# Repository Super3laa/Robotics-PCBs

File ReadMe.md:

# Robotics PCB

Some of PCB Designs during a robotics journey in college, There's more but i uploaded the cool ones, feel free to contact me about anything

### Tools
all of them deleoped using Eagle CAD.

### Open Source for Everyone Enjoy! :*

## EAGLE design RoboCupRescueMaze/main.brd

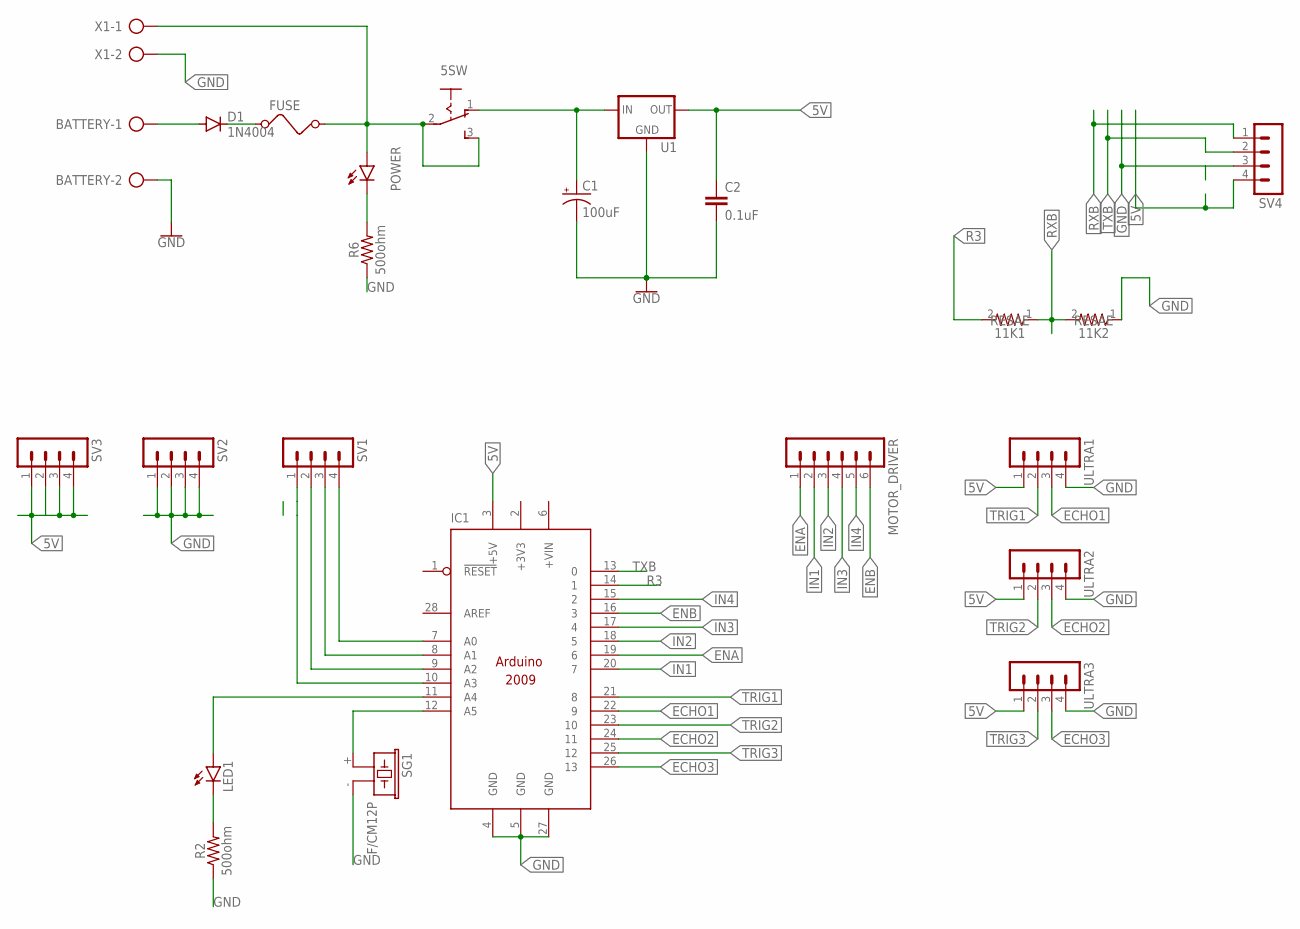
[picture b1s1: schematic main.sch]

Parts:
5SW: 255SB
11K1, 11K2: RESAE; RESAD846W63L520D250B
BATTERY: AK500/2-H
C1: 100uF; CPOL-RADIAL-2.5MM-6.5MM
C2: 0.1uF; CAP-PTH-SMALL-KIT
D1: 1N4004; DO41-10
FUSE: FUSE
IC1: ARDUINO2009_10; ARDUINO2009
LED1: LED10MM
MOTOR_DRIVER: MA06-1
POWER: LED3MM
R2, R6: 500ohm; AXIAL-0.3
SG1: F/CM12P
SV1, SV2, SV3, SV4: MA04-1
U1: 78XXS
ULTRA1, ULTRA2, ULTRA3: MA04-1
X1: AK500/2-H

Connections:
5V: C2.1, IC1.3 (+5V), SV3.1, SV3.2, SV3.3, SV3.4, SV4.4, U1.OUT, ULTRA1.1, ULTRA2.1, ULTRA3.1
+3V3: IC1.2 (+3V3)
BATTERYI: BATTERY.1, D1.A
ECHO1: IC1.22 (9), ULTRA1.3
ECHO2: IC1.24 (11), ULTRA2.3
ECHO3: IC1.26 (13), ULTRA3.3
ENA: IC1.19 (6), MOTOR_DRIVER.1
ENB: IC1.16 (3), MOTOR_DRIVER.6
GND: 11K2.1, BATTERY.2, C1.2 (-), C2.2, IC1.4 (GND), IC1.5 (GND), IC1.27 (GND), R2.P$1 (1), R6.P$1 (1), SG1.- (2), SV2.1, SV2.2, SV2.3, SV2.4, SV4.3, U1.GND, ULTRA1.4, ULTRA2.4, ULTRA3.4, X1.2
IN1: IC1.20 (7), MOTOR_DRIVER.2
IN2: IC1.18 (5), MOTOR_DRIVER.3
IN3: IC1.17 (4), MOTOR_DRIVER.4
IN4: IC1.15 (2), MOTOR_DRIVER.5
unnamed: IC1.7 (A0), SV1.4
unnamed: IC1.8 (A1), SV1.3
unnamed: IC1.9 (A2), SV1.2
unnamed: IC1.10 (A3), SV1.1
unnamed: IC1.11 (A4), LED1.A
unnamed: D1.C, FUSE.1
unnamed: POWER.K (C), R6.P$2 (2)
unnamed: 5SW.2, 5SW.3 (S), FUSE.2, POWER.A, X1.1
unnamed: LED1.K (C), R2.P$2 (2)
unnamed: IC1.12 (A5), SG1.+ (1)
R3: 11K1.2, IC1.14 (1)
RXB: 11K1.1, 11K2.2, SV4.1
SSS: 5SW.1 (O), C1.1 (+), U1.IN
TRIG1: IC1.21 (8), ULTRA1.2
TRIG2: IC1.23 (10), ULTRA2.2
TRIG3: IC1.25 (12), ULTRA3.2
TXB: IC1.13 (0), SV4.2

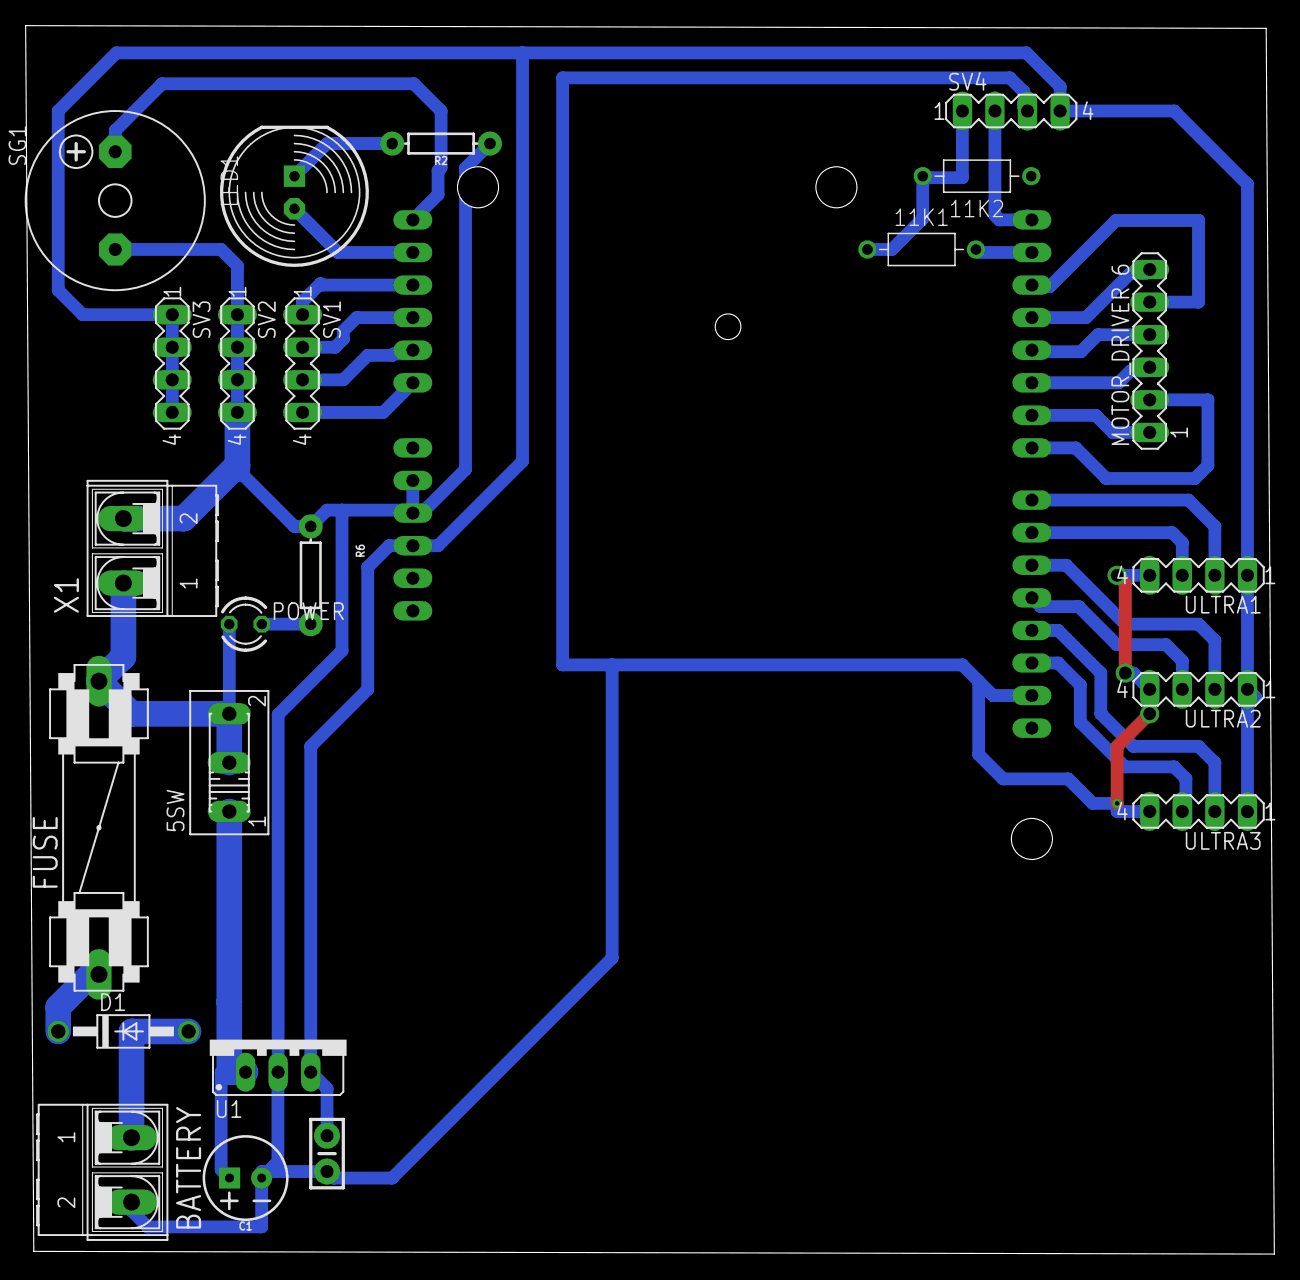
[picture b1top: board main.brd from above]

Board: 2 copper layers, 97.3 x 95.8 mm, 24 parts (1 on the bottom side), 29 nets.

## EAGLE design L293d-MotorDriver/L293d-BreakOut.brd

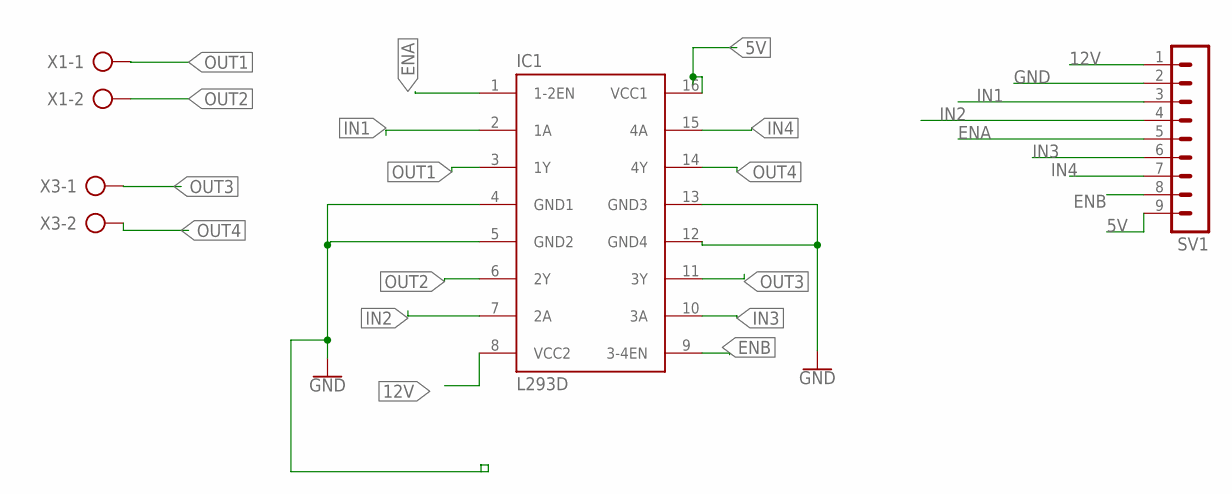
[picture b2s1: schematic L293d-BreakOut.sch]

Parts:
IC1: L293D; DIL16
SV1: MA09-1W
X1, X3: AK500/2-H

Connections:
5V: IC1.16 (VCC1), SV1.9
12V: IC1.8 (VCC2), SV1.1
ENA: IC1.1 (1-2EN), SV1.5
ENB: IC1.9 (3-4EN), SV1.8
GND: IC1.4 (GND1), IC1.5 (GND2), IC1.12 (GND4), IC1.13 (GND3), SV1.2
IN1: IC1.2 (1A), SV1.3
IN2: IC1.7 (2A), SV1.4
IN3: IC1.10 (3A), SV1.6
IN4: IC1.15 (4A), SV1.7
OUT1: IC1.3 (1Y), X1.1
OUT2: IC1.6 (2Y), X1.2
OUT3: IC1.11 (3Y), X3.1
OUT4: IC1.14 (4Y), X3.2

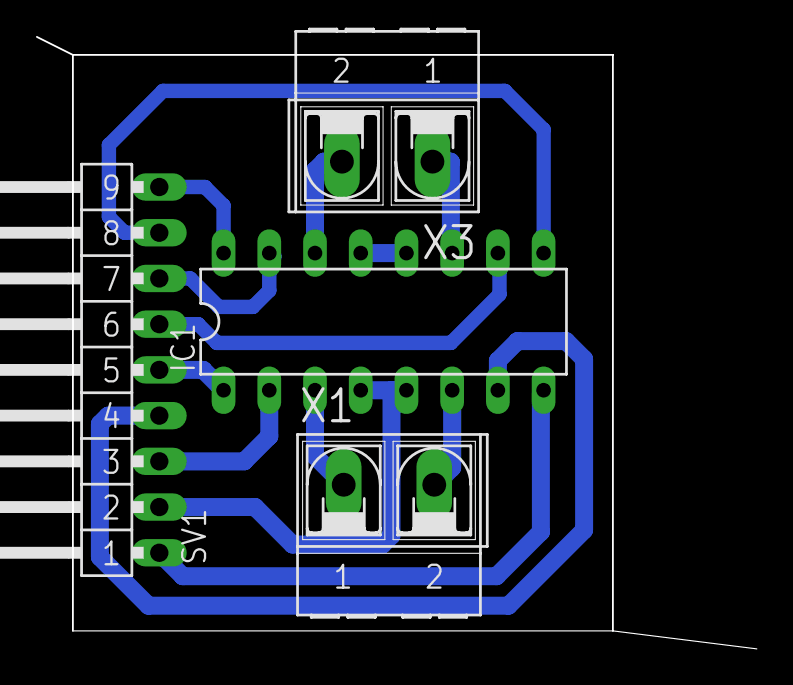
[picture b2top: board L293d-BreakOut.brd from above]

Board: 2 copper layers, 40.0 x 34.0 mm, 4 parts (0 on the bottom side), 13 nets.

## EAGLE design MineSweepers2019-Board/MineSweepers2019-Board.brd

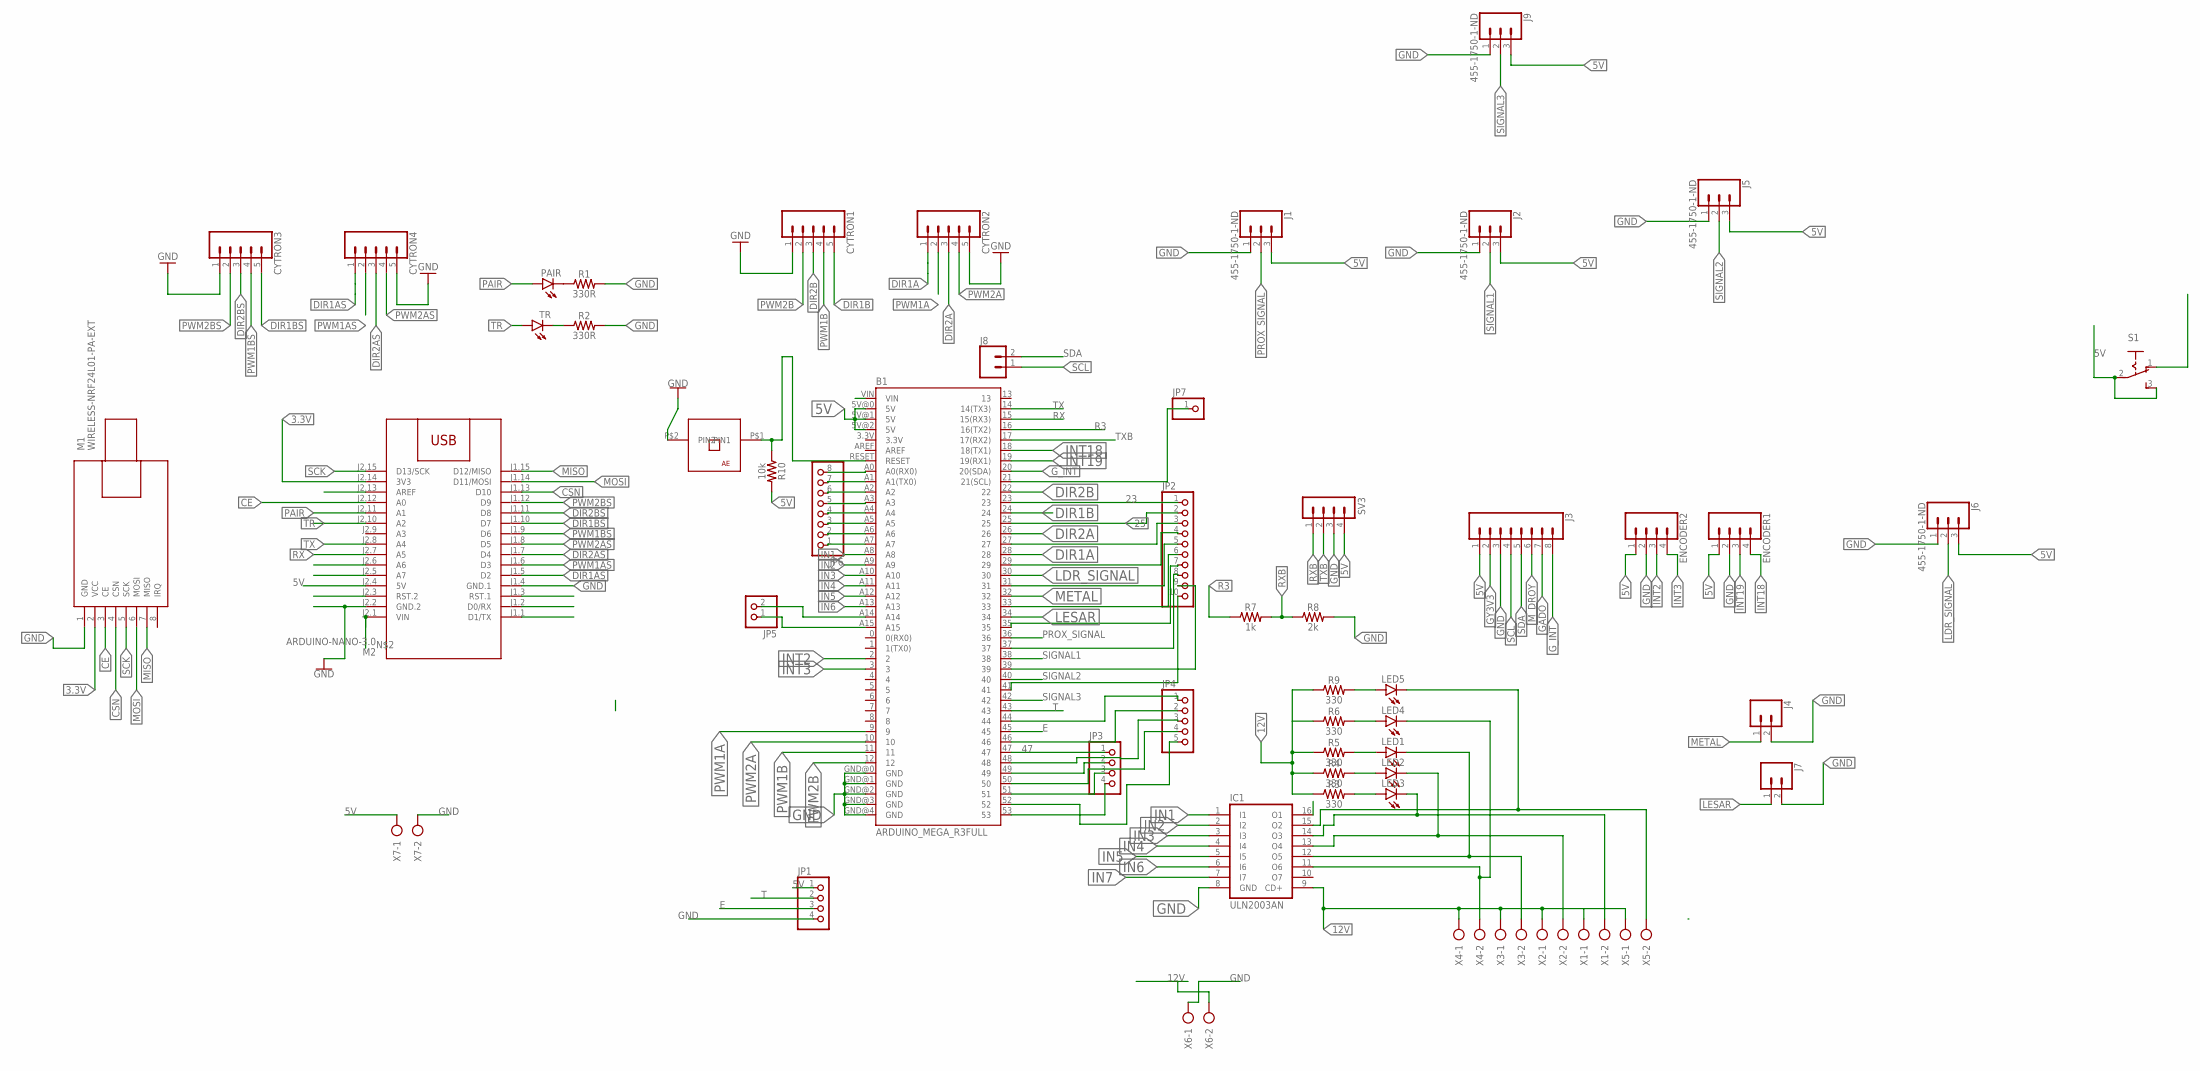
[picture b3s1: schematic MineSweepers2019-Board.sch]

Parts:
B1: ARDUINO_MEGA_R3FULL; ARDUINO_MEGA
CYTRON1, CYTRON2, CYTRON3, CYTRON4: CONN_05; 1X05
ENCODER1, ENCODER2: CONN_04; 1X04
IC1: ULN2003AN; DIL16
J1, J2, J5, J6, J9: 455-1750-1-ND; 1X03
J3: CONN_08"; 1X08
J4, J7, J8: CONN_02; 1X02
JP1, JP3: PINHD-1X4; 1X04
JP2: PINHD-1X10; 1X10
JP4: PINHD-1X5; 1X05
JP5: PINHD-1X2; 1X02
JP6: PINHD-1X8; 1X08
JP7: PINHD-1X1; 1X01
LED1, LED2, LED3, LED4, LED5: LED3MM
M1: WIRELESS-NRF24L01-PA-EXT
M2: ARDUINO-NANO-3.0
PAIR: LED3MM
R1, R2: 330R; AXIAL-0.3
R3, R4, R5, R6, R9: 330; AXIAL-0.3
R7: 1k; AXIAL-0.3
R8: 2k; AXIAL-0.3
R10: 10k; AXIAL-0.3
S1: 255SB
SV3: MA04-1
TR: LED3MM
U$1: PUSHBUTTON-AE
X1, X2, X3, X4, X5, X6, X7: AK500/2-H

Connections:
3.3V: M1.2 (VCC), M2.J2.14 (3V3)
5V: B1.5V@0 (5V), B1.5V@1 (5V), B1.5V@2 (5V), ENCODER1.1, ENCODER2.1, J1.3, J2.3, J3.1, J5.3, J6.3, J9.3, JP1.1, M2.J2.4 (5V), R10.P$2 (2), S1.2, S1.3 (S), SV3.4, X7.1
12V: IC1.9 (CD+), R3.P$1 (1), R4.P$1 (1), R5.P$1 (1), R6.P$1 (1), R9.P$1 (1), X1.1, X2.1, X3.1, X4.1, X5.1, X6.2
23: B1.23, JP2.1
25: B1.25, JP2.2
47: B1.47, JP3.1
CE: M1.3 (CE), M2.J2.12 (A0)
CSN: M1.4 (CSN), M2.J1.13 (D10)
DIR1A: B1.28, CYTRON2.1
DIR1AS: CYTRON4.1, M2.J1.5 (D2)
DIR1B: B1.24, CYTRON1.5
DIR1BS: CYTRON3.5, M2.J1.10 (D7)
DIR2A: B1.26, CYTRON2.3
DIR2AS: CYTRON4.3, M2.J1.7 (D4)
DIR2B: B1.22, CYTRON1.3
DIR2BS: CYTRON3.3, M2.J1.11 (D8)
E: B1.45, JP1.3
GADO: J3.7
GND: B1.GND@0 (GND), B1.GND@1 (GND), B1.GND@2 (GND), B1.GND@3 (GND), B1.GND@4 (GND), CYTRON1.1, CYTRON2.5, CYTRON3.1, CYTRON4.5, ENCODER1.2, ENCODER2.2, IC1.8 (GND), J1.1, J2.1, J3.3, J4.2, J5.1, J6.1, J7.2, J9.1, JP1.4, M1.1 (GND), M2.J1.4 (GND.1), M2.J2.2 (GND.2), R1.P$2 (2), R2.P$2 (2), R8.P$2 (2), SV3.3, U$1.P$2 (PIN2), X6.1, X7.2
GY3V3: J3.2
G_INT: B1.20 (20(SDA)), J3.8
IN1: B1.A8, IC1.1 (I1)
IN2: B1.A9, IC1.2 (I2)
IN3: B1.A10, IC1.3 (I3)
IN4: B1.A11, IC1.4 (I4)
IN5: B1.A12, IC1.5 (I5)
IN6: B1.A13, IC1.6 (I6)
IN7: IC1.7 (I7)
INT2: B1.2, ENCODER2.3
INT3: B1.3, ENCODER2.4
INT18: B1.18 (18(TX1)), ENCODER1.4
INT19: B1.19 (19(RX1)), ENCODER1.3
LDR_SIGNAL: B1.30, J6.2
LESAR: B1.34, J7.1
METAL: B1.32, J4.1
MISO: M1.7 (MISO), M2.J1.15 (D12/MISO)
MOSI: M1.6 (MOSI), M2.J1.14 (D11/MOSI)
M_DROY: J3.6
unnamed: LED5.A, R9.P$2 (2)
unnamed: PAIR.K (C), R1.P$1 (1)
unnamed: R2.P$1 (1), TR.K (C)
unnamed: B1.27, JP2.3
unnamed: IC1.13 (O4), LED2.K (C), X2.2
unnamed: IC1.14 (O3), LED3.K (C), X1.2
unnamed: IC1.12 (O5), LED1.K (C), X3.2
unnamed: B1.29, JP2.4
unnamed: B1.31, JP2.5
unnamed: B1.33, JP2.6
unnamed: B1.35, JP2.7
unnamed: LED3.A, R3.P$2 (2)
unnamed: LED2.A, R4.P$2 (2)
unnamed: B1.37, JP2.8
unnamed: LED1.A, R5.P$2 (2)
unnamed: B1.39, JP2.9
unnamed: B1.41, JP2.10
unnamed: B1.49, JP3.2
unnamed: B1.51, JP3.3
unnamed: LED4.A, R6.P$2 (2)
unnamed: B1.53, JP3.4
unnamed: B1.44, JP4.1
unnamed: B1.46, JP4.2
unnamed: B1.48, JP4.3
unnamed: B1.50, JP4.4
unnamed: B1.52, JP4.5
unnamed: B1.A1 (A1(TX0)), JP6.7
unnamed: B1.A2, JP6.6
unnamed: B1.A3, JP6.5
unnamed: B1.A4, JP6.4
unnamed: B1.A5, JP6.3
unnamed: B1.A6, JP6.2
unnamed: B1.A7, JP6.1
unnamed: B1.A0 (A0(RX0)), JP6.8
unnamed: B1.A14, JP5.2
unnamed: B1.A15, JP5.1
unnamed: B1.21 (21(SCL)), JP7.1
unnamed: B1.RESET, R10.P$1 (1), U$1.P$1 (PIN1)
O1: IC1.15 (O2), LED5.K (C), X5.2
O2: IC1.16 (O1)
O6: IC1.11 (O6), LED4.K (C), X4.2
PAIR: M2.J2.11 (A1), PAIR.A
PROX_SIGNAL: B1.36, J1.2
PWM1A: B1.9, CYTRON2.2
PWM1AS: CYTRON4.2, M2.J1.6 (D3)
PWM1B: B1.11, CYTRON1.4
PWM1BS: CYTRON3.4, M2.J1.9 (D6)
PWM2A: B1.10, CYTRON2.4
PWM2AS: CYTRON4.4, M2.J1.8 (D5)
PWM2B: B1.12, CYTRON1.2
PWM2BS: CYTRON3.2, M2.J1.12 (D9)
R3: B1.16 (16(TX2)), R7.P$1 (1)
RX: B1.15 (15(RX3)), M2.J2.7 (A5)
RXB: R7.P$2 (2), R8.P$1 (1), SV3.1
SCK: M1.5 (SCK), M2.J2.15 (D13/SCK)
SCL: J3.4, J8.1
SDA: J3.5, J8.2
SIGNAL1: B1.38, J2.2
SIGNAL2: B1.40, J5.2
SIGNAL3: B1.42, J9.2
T: B1.43, JP1.2
TR: M2.J2.10 (A2), TR.A
TX: B1.14 (14(TX3)), M2.J2.8 (A4)
TXB: B1.17 (17(RX2)), SV3.2
VIN: B1.VIN

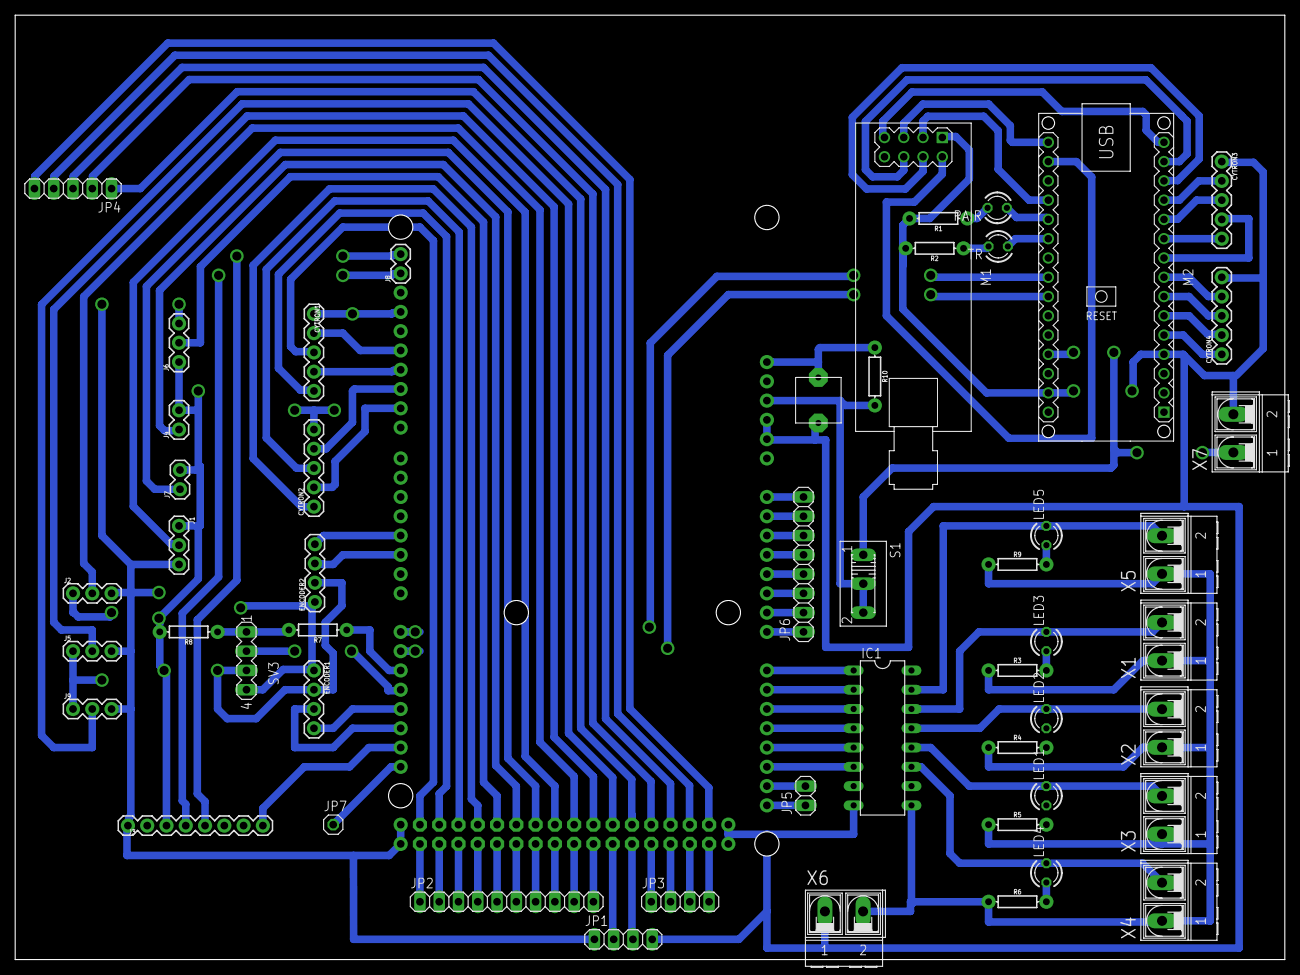
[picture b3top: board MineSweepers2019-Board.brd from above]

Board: 2 copper layers, 167.3 x 124.5 mm, 53 parts (1 on the bottom side), 97 nets.

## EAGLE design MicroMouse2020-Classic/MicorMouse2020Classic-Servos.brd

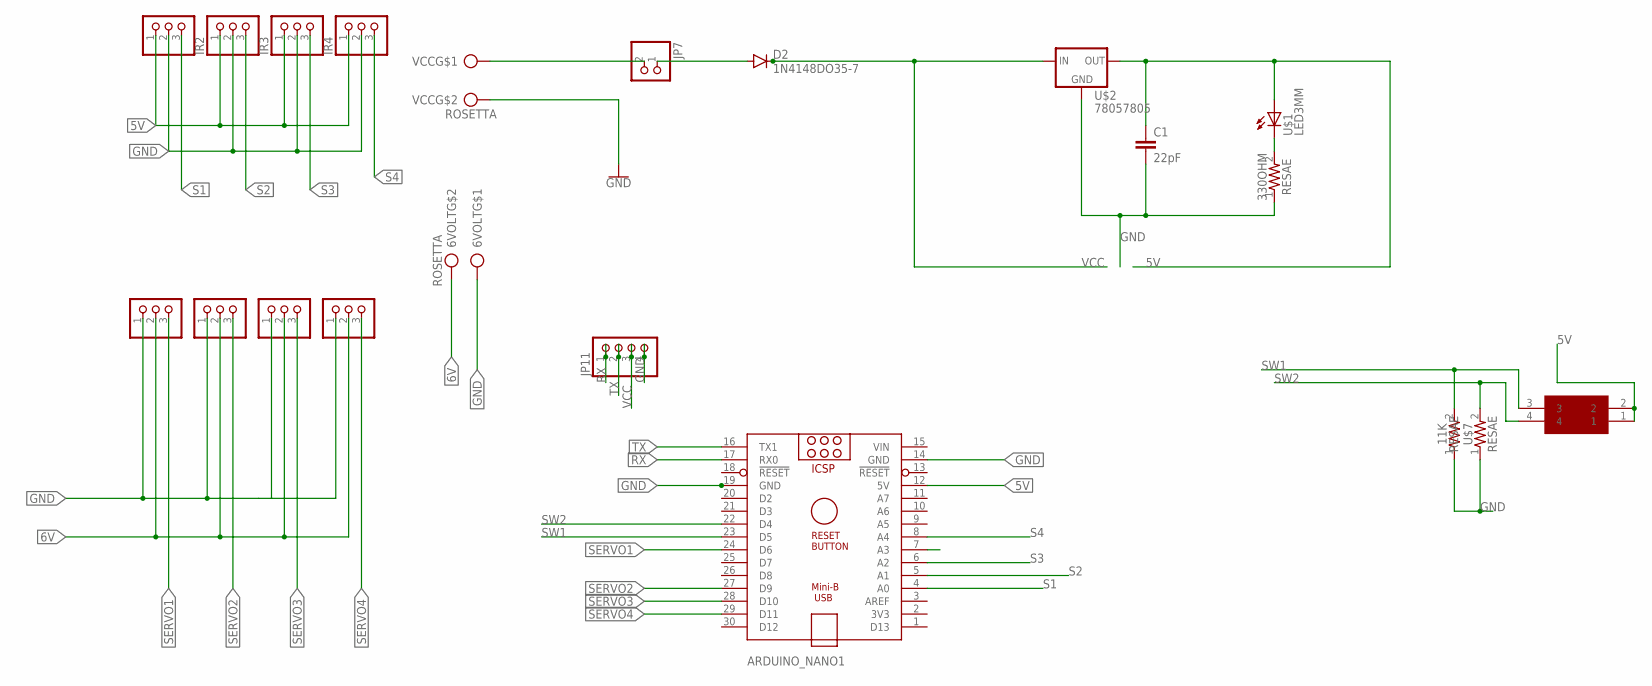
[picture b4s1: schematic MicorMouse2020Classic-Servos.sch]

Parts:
6VOLT: ROSETTA; AK550/2
11K, 330OHM: RESAE; RESAD846W63L520D250B
ARDUINO_NANO1: ARDUINO_NANO
C1: 22pF; CAP-PTH-2.54
D2: 1N4148DO35-7; DO35-7
IR1, IR2, IR3, IR4: PINHD-1X3; 1X03
JP7: PINHD-1X2; 1X02
JP11: PINHD-1X4/90; 1X04/90
SERVO1, SERVO2, SERVO3, SERVO4: PINHD-1X3; 1X03
U$1: LED3MM; LEDRD254W60D310H860B
U$2: 78057805; T-30_V
U$7: RESAE; RESAD846W63L520D250B
U$8: AE-DIP; EPG-02
VCC: ROSETTA; AK550/2

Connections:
5V: ARDUINO_NANO1.12 (5V), C1.1, IR1.1, IR2.1, IR3.1, IR4.1, U$1.A, U$2.3 (OUT), U$8.1, U$8.2
6V: 6VOLT.2, SERVO1.2, SERVO2.2, SERVO3.2, SERVO4.2
GND: 6VOLT.1, 11K.1, 330OHM.1, ARDUINO_NANO1.14 (GND), ARDUINO_NANO1.19 (GND), C1.2, IR1.2, IR2.2, IR3.2, IR4.2, JP11.4, SERVO1.1, SERVO2.1, SERVO3.1, SERVO4.1, U$2.2 (GND), U$7.1, VCC.2
unnamed: JP7.2, VCC.1
unnamed: D2.A, JP7.1
unnamed: 330OHM.2, U$1.C
RX: ARDUINO_NANO1.17 (RX0), JP11.1
S1: ARDUINO_NANO1.4 (A0), IR1.3
S2: ARDUINO_NANO1.5 (A1), IR2.3
S3: ARDUINO_NANO1.6 (A2), IR3.3
S4: ARDUINO_NANO1.8 (A4), IR4.3
SERVO1: ARDUINO_NANO1.24 (D6), SERVO4.3
SERVO2: ARDUINO_NANO1.27 (D9), SERVO3.3
SERVO3: ARDUINO_NANO1.28 (D10), SERVO2.3
SERVO4: ARDUINO_NANO1.29 (D11), SERVO1.3
SW1: 11K.2, ARDUINO_NANO1.23 (D5), U$8.3
SW2: ARDUINO_NANO1.22 (D4), U$7.2, U$8.4
TX: ARDUINO_NANO1.16 (TX1), JP11.2
VCC: D2.C, JP11.3, U$2.1 (IN)
VIN: ARDUINO_NANO1.15 (VIN)

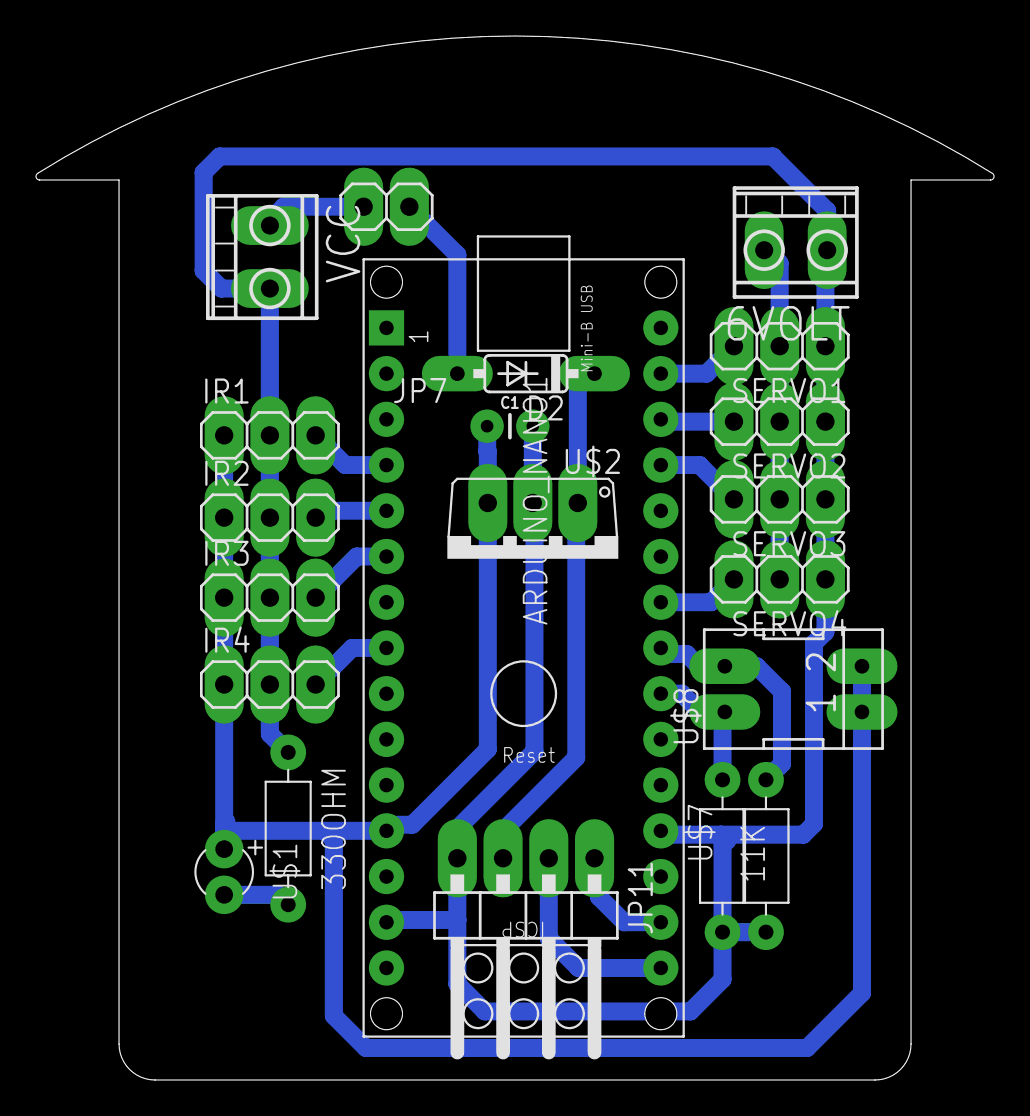
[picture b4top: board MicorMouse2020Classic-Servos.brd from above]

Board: 2 copper layers, 53.2 x 58.0 mm, 21 parts (0 on the bottom side), 19 nets.

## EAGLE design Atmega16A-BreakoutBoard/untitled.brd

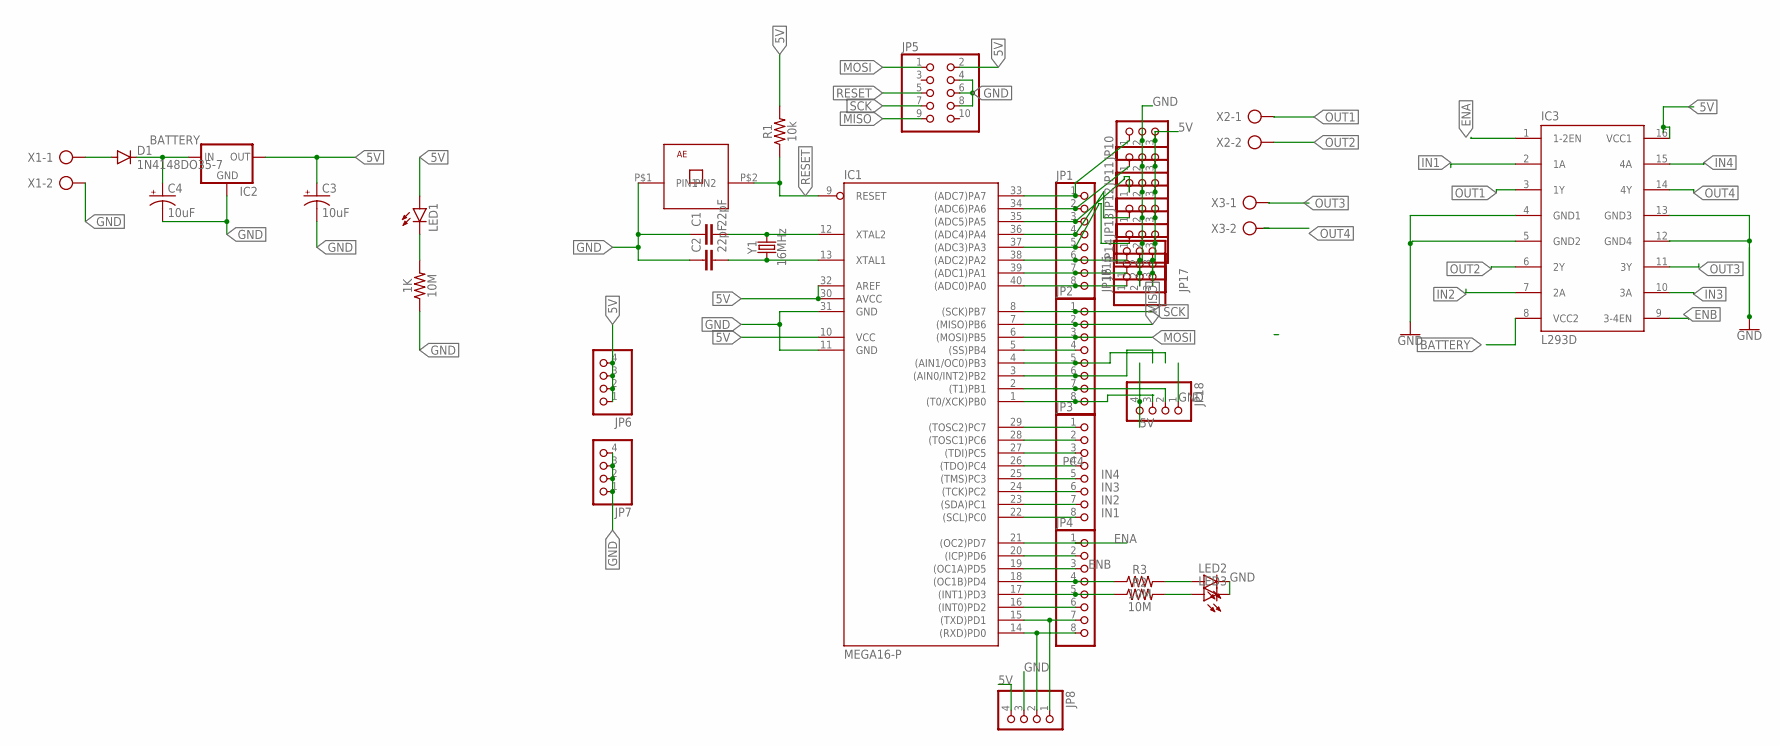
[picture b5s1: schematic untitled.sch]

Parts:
1K: 10M; AXIAL-0.3
C1, C2: 22pF; CAP-PTH-2.54
C3, C4: 10uF; CPOL-RADIAL-2.5MM-5MM
D1: 1N4148DO35-7; DO35-7
IC1: MEGA16-P; DIL40
IC2: 78XXS
IC3: L293D; DIL16
JP1, JP2, JP3, JP4: PINHD-1X8; 1X08
JP5: PINHD-2X5; 2X05
JP6, JP7, JP8, JP18: PINHD-1X4; 1X04
JP10, JP11, JP12, JP13, JP14, JP15, JP16, JP17: PINHD-1X3; 1X03
LED1, LED2, LED3: LED3MM
R1: 10k; AXIAL-0.3
R2, R3: 10M; AXIAL-0.3
U$1: PUSHBUTTON-AE
X1, X2, X3: AK500/2-H
Y1: 16MHz; HC49US

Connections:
5V: C3.1 (+), IC1.10 (VCC), IC1.30 (AVCC), IC1.32 (AREF), IC2.OUT, IC3.16 (VCC1), JP5.2, JP6.1, JP6.2, JP6.3, JP6.4, JP8.4, JP10.3, JP11.3, JP12.3, JP13.3, JP14.3, JP15.3, JP16.3, JP17.3, JP18.4, LED1.A, R1.P$2 (2)
BATTERY: C4.1 (+), D1.C, IC2.IN, IC3.8 (VCC2)
ENA: IC1.21 ((OC2)PD7), IC3.1 (1-2EN), JP4.1
ENB: IC1.19 ((OC1A)PD5), IC3.9 (3-4EN), JP4.3
GND: 1K.P$1 (1), C1.1, C2.1, C3.2 (-), C4.2 (-), IC1.11 (GND), IC1.31 (GND), IC2.GND, IC3.4 (GND1), IC3.5 (GND2), IC3.12 (GND4), IC3.13 (GND3), JP5.4, JP5.6, JP5.8, JP7.1, JP7.2, JP7.3, JP7.4, JP8.3, JP10.2, JP11.2, JP12.2, JP13.2, JP14.2, JP15.2, JP16.2, JP17.2, JP18.1, LED2.K (C), LED3.K (C), U$1.P$1 (PIN1), X1.2
IN1: IC1.22 ((SCL)PC0), IC3.2 (1A), JP3.8
IN2: IC1.23 ((SDA)PC1), IC3.7 (2A), JP3.7
IN3: IC1.24 ((TCK)PC2), IC3.10 (3A), JP3.6
IN4: IC1.25 ((TMS)PC3), IC3.15 (4A), JP3.5
MISO: IC1.7 ((MISO)PB6), JP2.2, JP5.9
MOSI: IC1.6 ((MOSI)PB5), JP2.3, JP5.1
unnamed: C1.2, IC1.12 (XTAL2), Y1.2
unnamed: C2.2, IC1.13 (XTAL1), Y1.1
unnamed: LED2.A, R3.P$2 (2)
unnamed: 1K.P$2 (2), LED1.K (C)
unnamed: LED3.A, R2.P$2 (2)
unnamed: D1.A, X1.1
unnamed: IC1.33 ((ADC7)PA7), JP1.1, JP10.1
unnamed: IC1.34 ((ADC6)PA6), JP1.2, JP11.1
unnamed: IC1.35 ((ADC5)PA5), JP1.3, JP12.1
unnamed: IC1.36 ((ADC4)PA4), JP1.4, JP13.1
unnamed: IC1.37 ((ADC3)PA3), JP1.5, JP14.1
unnamed: IC1.38 ((ADC2)PA2), JP1.6, JP15.1
unnamed: IC1.39 ((ADC1)PA1), JP1.7, JP16.1
unnamed: IC1.40 ((ADC0)PA0), JP1.8, JP17.1
unnamed: IC1.5 ((SS)PB4), JP2.4
unnamed: IC1.4 ((AIN1/OC0)PB3), JP2.5
unnamed: IC1.3 ((AIN0/INT2)PB2), JP2.6
unnamed: IC1.2 ((T1)PB1), JP2.7, JP18.2
unnamed: IC1.1 ((T0/XCK)PB0), JP2.8, JP18.3
unnamed: IC1.29 ((TOSC2)PC7), JP3.1
unnamed: IC1.28 ((TOSC1)PC6), JP3.2
unnamed: IC1.27 ((TDI)PC5), JP3.3
unnamed: IC1.20 ((ICP)PD6), JP4.2
unnamed: IC1.18 ((OC1B)PD4), JP4.4, R3.P$1 (1)
unnamed: IC1.17 ((INT1)PD3), JP4.5, R2.P$1 (1)
unnamed: IC1.16 ((INT0)PD2), JP4.6
OUT1: IC3.3 (1Y), X2.1
OUT2: IC3.6 (2Y), X2.2
OUT3: IC3.11 (3Y), X3.1
OUT4: IC3.14 (4Y), X3.2
PC4: IC1.26 ((TDO)PC4), JP3.4
RESET: IC1.9 (RESET), JP5.5, R1.P$1 (1), U$1.P$2 (PIN2)
RX: IC1.14 ((RXD)PD0), JP4.8, JP8.2
SCK: IC1.8 ((SCK)PB7), JP2.1, JP5.7
TX: IC1.15 ((TXD)PD1), JP4.7, JP8.1

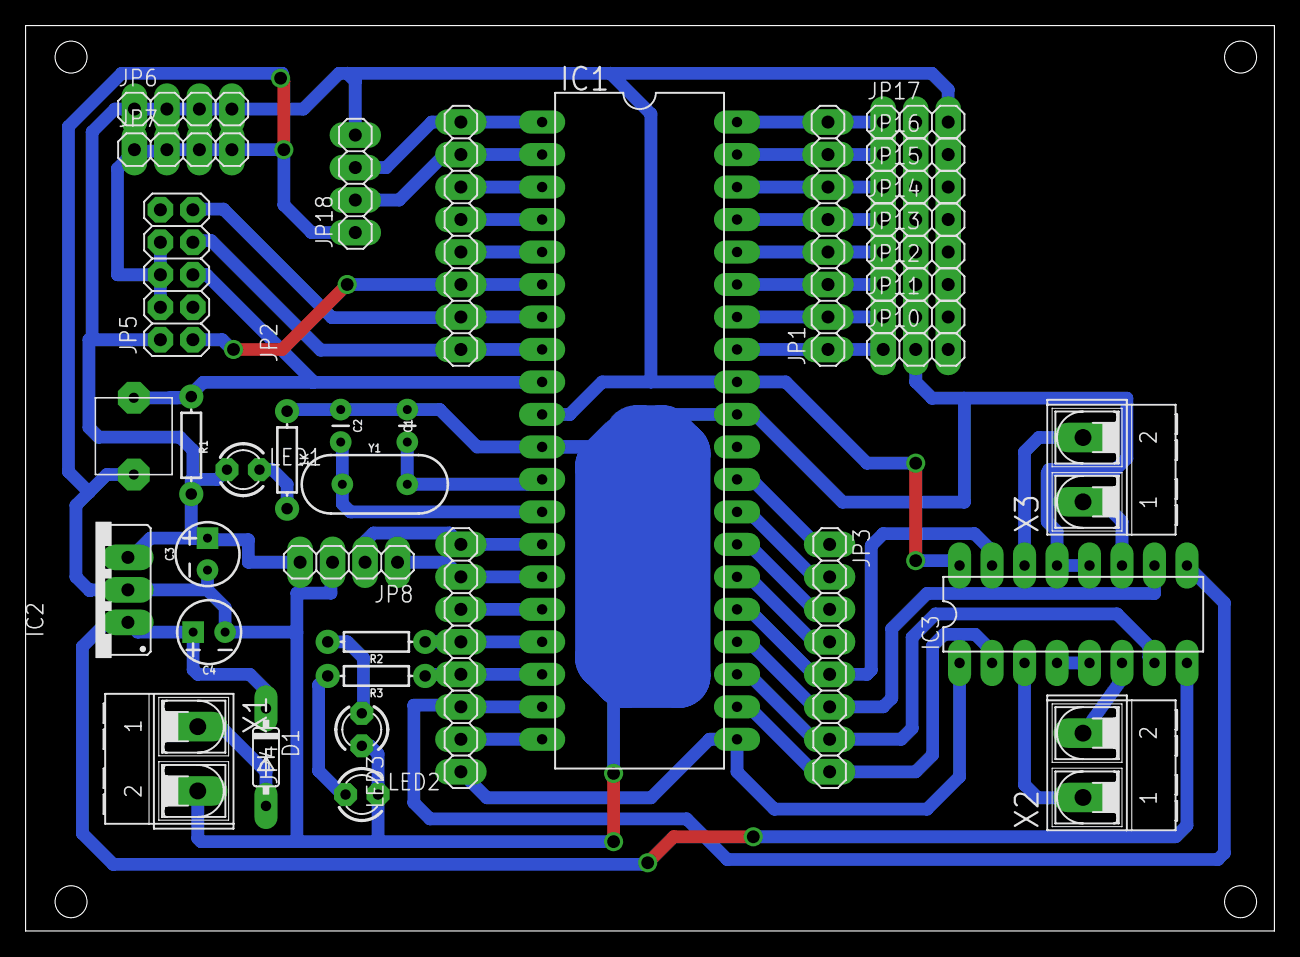
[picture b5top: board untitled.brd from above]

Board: 2 copper layers, 97.6 x 70.8 mm, 37 parts (0 on the bottom side), 46 nets.

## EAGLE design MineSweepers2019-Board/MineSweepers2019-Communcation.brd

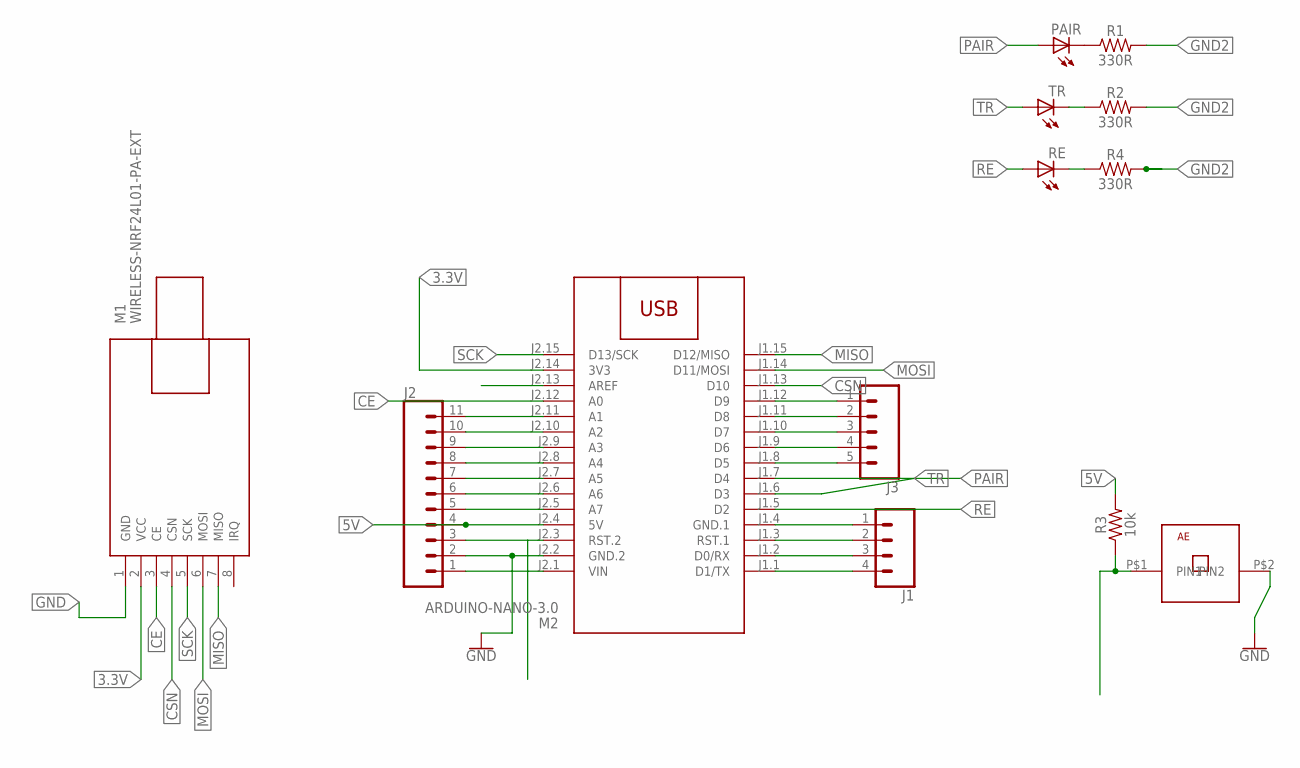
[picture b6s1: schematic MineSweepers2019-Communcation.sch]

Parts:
J1: CONN_04; 1X04
J2: CONN_11; 1X11
J3: CONN_05; 1X05
M1: WIRELESS-NRF24L01-PA-EXT
M2: ARDUINO-NANO-3.0
PAIR: LED3MM
R1, R2, R4: 330R; AXIAL-0.3
R3: 10k; AXIAL-0.3
RE: LED3MM
TR: LED3MM
U$1: PUSHBUTTON-AE

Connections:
3.3V: M1.2 (VCC), M2.J2.14 (3V3)
5V: J2.4, M2.J2.4 (5V), R3.P$2 (2)
CE: M1.3 (CE), M2.J2.12 (A0)
CSN: M1.4 (CSN), M2.J1.13 (D10)
GND: J2.2, M1.1 (GND), M2.J2.2 (GND.2), U$1.P$2 (PIN2)
GND2: J1.1, M2.J1.4 (GND.1), R1.P$2 (2), R2.P$2 (2), R4.P$2 (2)
MISO: M1.7 (MISO), M2.J1.15 (D12/MISO)
MOSI: M1.6 (MOSI), M2.J1.14 (D11/MOSI)
unnamed: J1.2, M2.J1.3 (RST.1)
unnamed: J3.3, M2.J1.10 (D7)
unnamed: J3.2, M2.J1.11 (D8)
unnamed: J3.1, M2.J1.12 (D9)
unnamed: PAIR.K (C), R1.P$1 (1)
unnamed: R2.P$1 (1), TR.K (C)
unnamed: J2.11, M2.J2.11 (A1)
unnamed: J2.10, M2.J2.10 (A2)
unnamed: J2.9, M2.J2.9 (A3)
unnamed: J2.8, M2.J2.8 (A4)
unnamed: J2.7, M2.J2.7 (A5)
unnamed: J2.6, M2.J2.6 (A6)
unnamed: J2.5, M2.J2.5 (A7)
unnamed: R4.P$1 (1), RE.K (C)
unnamed: J2.3, M2.J2.3 (RST.2)
unnamed: J3.4, M2.J1.9 (D6)
unnamed: J2.1, M2.J2.1 (VIN)
unnamed: J3.5, M2.J1.8 (D5)
unnamed: J1.3, M2.J1.2 (D0/RX)
unnamed: J1.4, M2.J1.1 (D1/TX)
unnamed: R3.P$1 (1), U$1.P$1 (PIN1)
PAIR: M2.J1.7 (D4), PAIR.A
RE: M2.J1.5 (D2), RE.A
SCK: M1.5 (SCK), M2.J2.15 (D13/SCK)
TR: M2.J1.6 (D3), TR.A

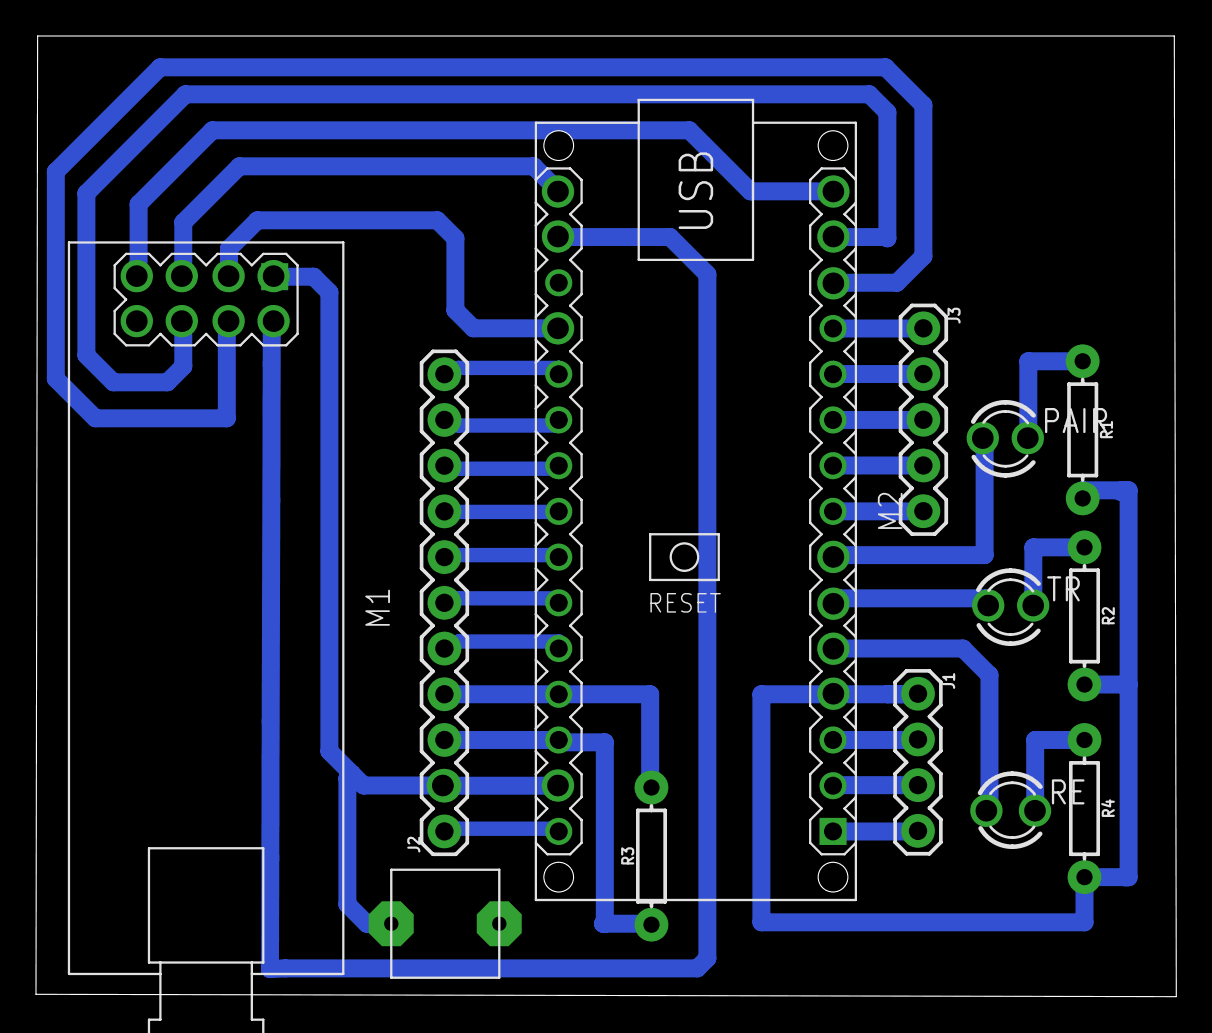
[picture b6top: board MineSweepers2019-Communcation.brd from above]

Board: 2 copper layers, 63.3 x 53.4 mm, 13 parts (0 on the bottom side), 33 nets.

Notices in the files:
parts and their libraries:
SparkFun-Resistors: Licensing: Creative Commons ShareAlike 4.0 International - https://creativecommons.org/licenses/by-sa/4.0
diy-modules: Released under the Creative Commons Attribution 4.0 International License: http://creativecommons.org/licenses/by/4.0
